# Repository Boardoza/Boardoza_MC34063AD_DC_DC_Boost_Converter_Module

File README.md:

# Boardoza MC34063A DC-DC Boost Converter Module

The **Boardoza MC34063A DC-DC Boost Converter Module** is a compact and efficient voltage step-up solution built around the reliable **MC34063A switching regulator IC**. This module is designed to convert a low DC input voltage into a higher regulated DC output voltage using a boost converter topology. With integrated current limiting and feedback regulation, the board provides stable and dependable power conversion for a wide variety of embedded and electronic applications.

Thanks to its compact PCB design and minimal external component requirement, this module is ideal for powering sensors, portable electronics, battery-operated systems, DIY electronics projects, and industrial control systems. The onboard status LED provides quick visual feedback for output operation, while the regulated switching architecture ensures efficient energy transfer and reduced power loss compared to linear regulator solutions.

## [Click here to purchase!](https://www.ozdisan.com/p/moduller-870/boardoza-mc34063ad-module-1591108?categoryName=moduller-870&productSlug=boardoza-mc34063ad-module-1591108)

|Front Side|Back Side|
|:---:|:---:|
| | |

---

## Key Features

- **Efficient DC-DC Boost Conversion:** Converts low DC input voltages into a stable higher output voltage.
- **Regulated Output Control:** Maintains consistent output voltage using an internal feedback regulation system.
- **Integrated Current Protection:** Includes short-circuit current limiting for improved reliability and safer operation.
- **Low Component Count:** Simplified external circuitry reduces design complexity and improves usability.
- **Status LED Indicator:** Onboard LED provides quick visual confirmation of output operation.
- **Suitable for Multiple Applications:** Ideal for embedded systems, DIY electronics, battery-powered devices, and power management projects.

---

## Technical Specifications

**Model:** MC34063AD   
**Manufacturer:** Boardoza  
**Manufacturer IC:** Texas Instruments      
**Functions:** DC-DC Boost Converter     
**Converter Topology:** Step-Up (Boost) Switching Regulator  
**Input Voltage:** 3 VDC to 12 VDC  
**Output Voltage:** 12 VDC Regulated  
**Output Current:** Up to 800mA  
**Switching Frequency:** Up to 100kHz  
**Reference Voltage Accuracy:** ±2%  
**Current Limiting:** Internal Short-Circuit Current Limiting  
**Operating Temperature:** 0°C to +75°C  
**Board Dimensions:** 40mm x 20mm  

---

## Board Pinout

### ( J1 ) Power Input Connector

| Pin Number | Pin Name | Description |
| :---: | :---: | --- |
| 1 | VIN | DC Input Voltage (3 VDC to 12 VDC) |
| 2 | GND | Ground |

### ( J2 ) Power Output Connector

| Pin Number | Pin Name | Description |
| :---: | :---: | --- |
| 1 | VOUT | Regulated 12 VDC Output |
| 2 | GND | Ground |

---

## Board Dimensions

---

## Step Files

[Boardoza MC34063AD.step](./assets/MC34063A%20Step.step)

---

## Datasheet

[MC34063A Datasheet.pdf](./assets/MC34063A%20Datasheet.pdf)

---

## Version History

- V1.0.0 - Initial Release

---

## Support

- If you have any questions or need support, please contact support@boardoza.com

---

## **License**
### **Hardware Design**

[![CC BY-SA 4.0][cc-by-sa-shield]][cc-by-sa]

All hardware design files are licensed under [Creative Commons Attribution-ShareAlike 4.0 International License][cc-by-sa].

[cc-by-sa]: http://creativecommons.org/licenses/by-sa/4.0/
[cc-by-sa-shield]: https://img.shields.io/badge/License-CC%20BY--SA%204.0-lightgrey.svg

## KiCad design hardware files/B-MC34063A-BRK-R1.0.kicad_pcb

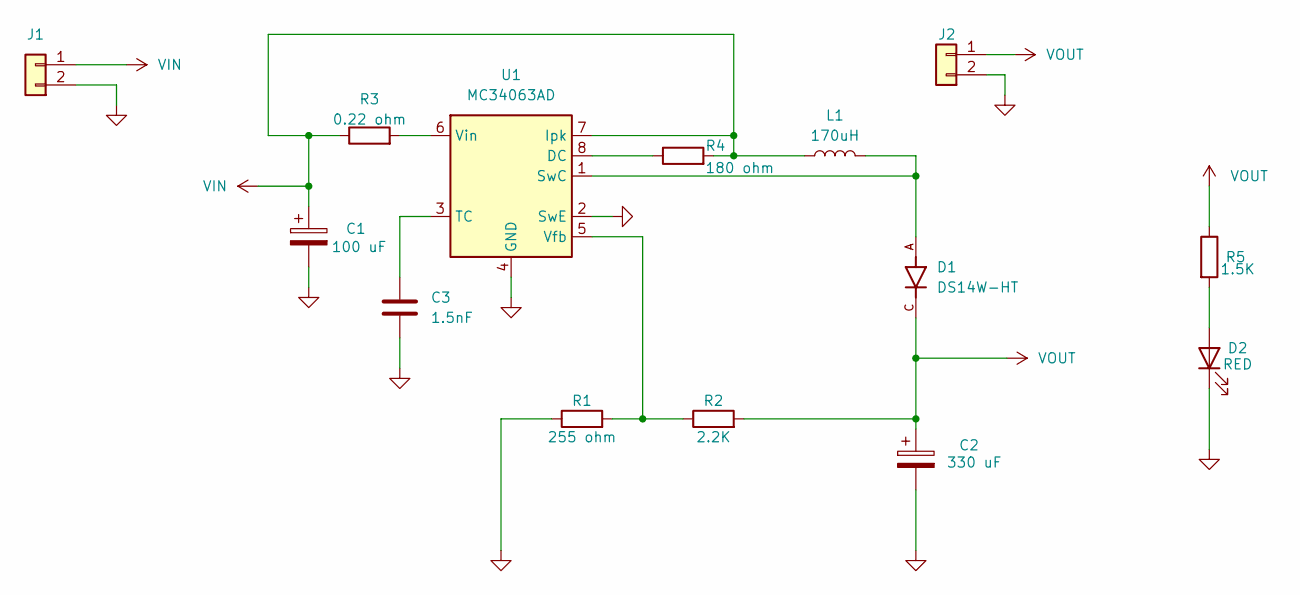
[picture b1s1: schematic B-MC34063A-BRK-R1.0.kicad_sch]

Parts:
C1: 100 uF; CP_Radial_D6.3mm_P2.50mm; MPN PF1V101MP26311UB7
C2: 330 uF; CP_Radial_D12.5mm_P5.00mm; MPN PKLH-063V331MH200
C3: 1.5nF; C_0603_1608Metric; MPN CL10B152JB8NNNC
D1: DS14W-HT; SODFL3816X120N; PARTREV 2021-07-12
D2: RED; LED_0603_1608Metric; MPN LTST-C190KRKT
J1, J2: Conn_01x02; 2317-02S_1x02_P2.50mm_Vertical; MPN 2317-02S
L1: 170uH; L_10.4x10.4_H4.8; MPN FPI1005-181M
R1: 255 ohm; R_0603_1608Metric; MPN 0603SAF2550T5E
R2: 2.2K; R_0603_1608Metric; MPN HP03W5F2201T5E
R3: 0.22 ohm; R_1206_3216Metric; MPN 1206S4F220LT5E
R4: 180 ohm; R_0603_1608Metric; MPN 0603SAJ0181T5E
R5: 1.5K; R_0603_1608Metric; MPN PS03W4F1501T5E
U1: MC34063AD; SOIC-8_3.9x4.9mm_P1.27mm; MPN MC34063AD-HTC

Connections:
GND: C1.2, C2.2, C3.2, D2.1 (K), J1.2, J2.2, R1.1, U1.2 (SwE), U1.4 (GND)
unnamed: D2.2 (A), R5.2
unnamed: R4.1, U1.8 (DC)
unnamed: D1.A, L1.2, U1.1 (SwC)
unnamed: C3.1, U1.3 (TC)
unnamed: R1.2, R2.1, U1.5 (Vfb)
unnamed: R3.2, U1.6 (Vin)
VIN: C1.1, J1.1, L1.1, R3.1, R4.2, U1.7 (Ipk)
VOUT: C2.1, D1.C, J2.1, R2.2, R5.1

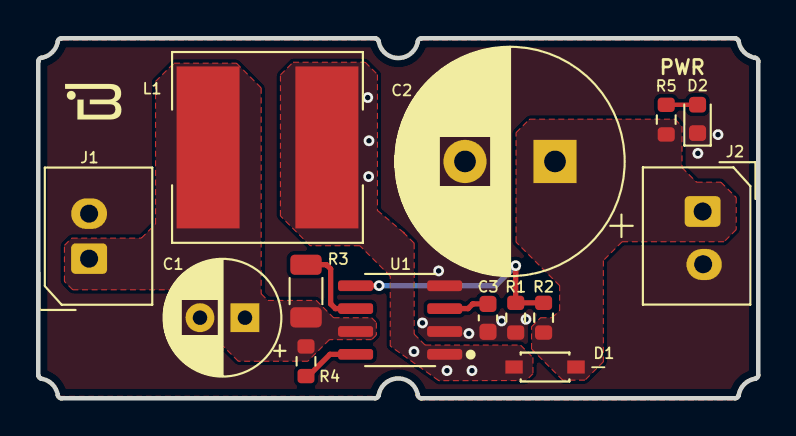
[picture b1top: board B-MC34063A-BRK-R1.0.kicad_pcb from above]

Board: 2 copper layers, 40.0 x 20.0 mm, 14 parts (0 on the bottom side), 9 nets.
